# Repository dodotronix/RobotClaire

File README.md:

# ROBOT CLAIRE
This project is the result of three years of development from my high school
years. The main goal was to build my own robot from scratch, without using
common construction parts that are readily available in many hobbyist shops
today.

At the time when I was creating my robot, open-source CAD programs weren’t at a
sufficient level to design something that could be sent to a factory for
fabrication. For this reason, the mechanical design was created using Inventor
2013, while the electronic design was done using KiCad. The project has already
gone through three upgrades, but the first one wasn’t documented. However, I
did take some photos to capture the atmosphere of the very first steps in
development ([claire-rev0](https://drive.google.com/open?id=1PmOoYiifd_Xv0sS2DL9yxbEeKM7cLnv_)).

## NAVIGATION IN PROJECT
In the following folders, you will find README.md files with more detailed
descriptions of the content. Some folders also include additional information,
such as installation and execution instructions, particularly in directories
containing software. Please note that this repository is still under
development, and not all folders have been fully uploaded yet.

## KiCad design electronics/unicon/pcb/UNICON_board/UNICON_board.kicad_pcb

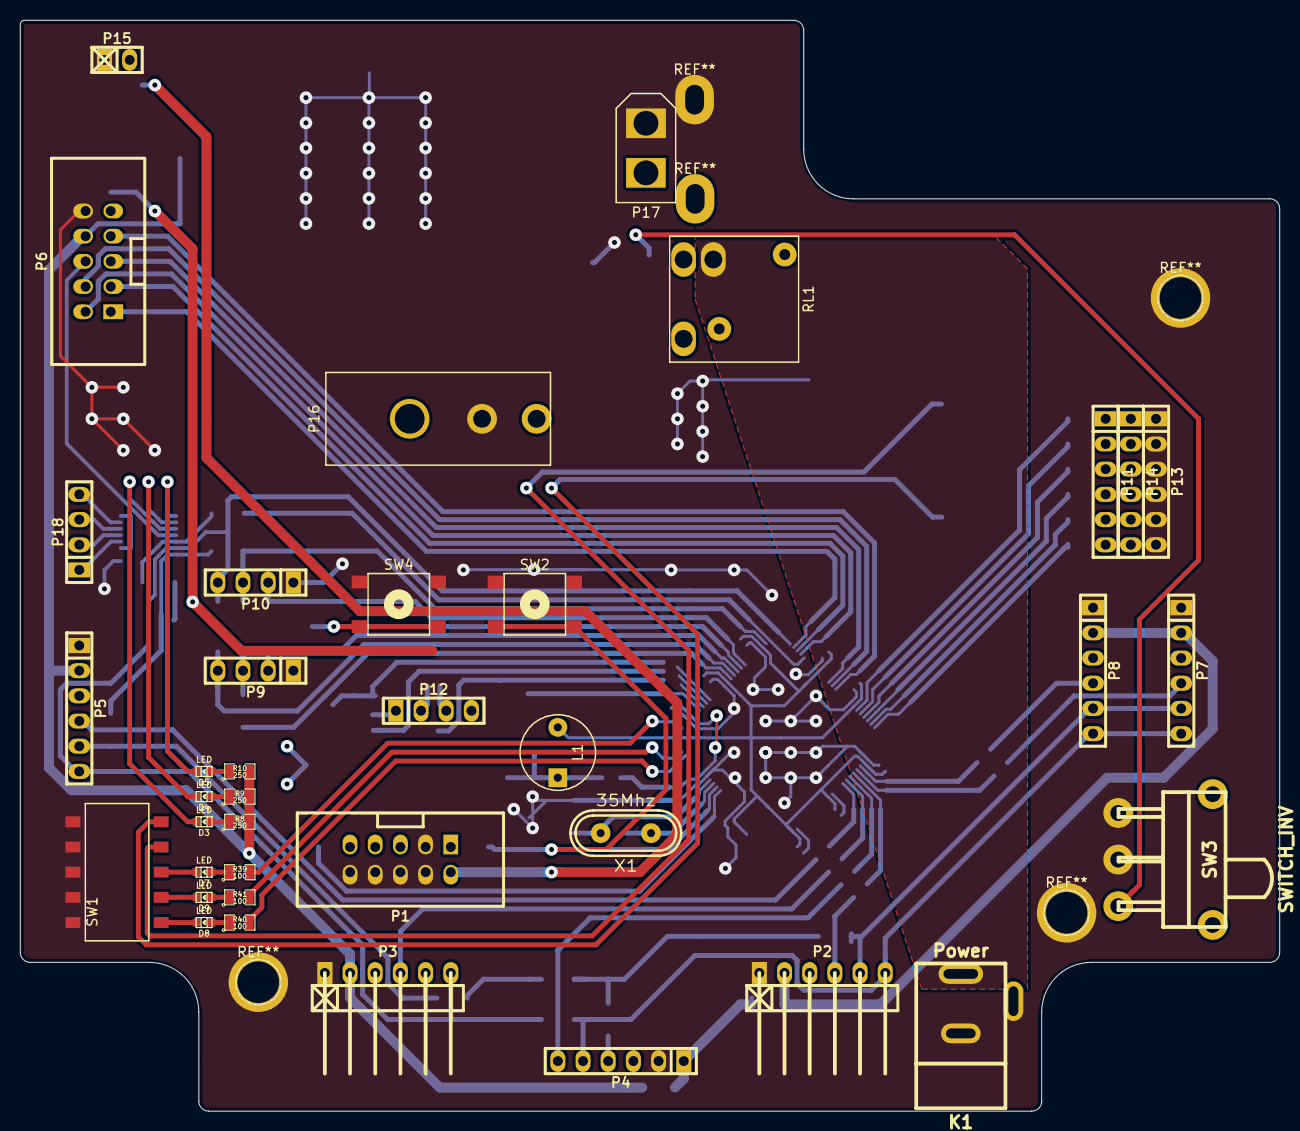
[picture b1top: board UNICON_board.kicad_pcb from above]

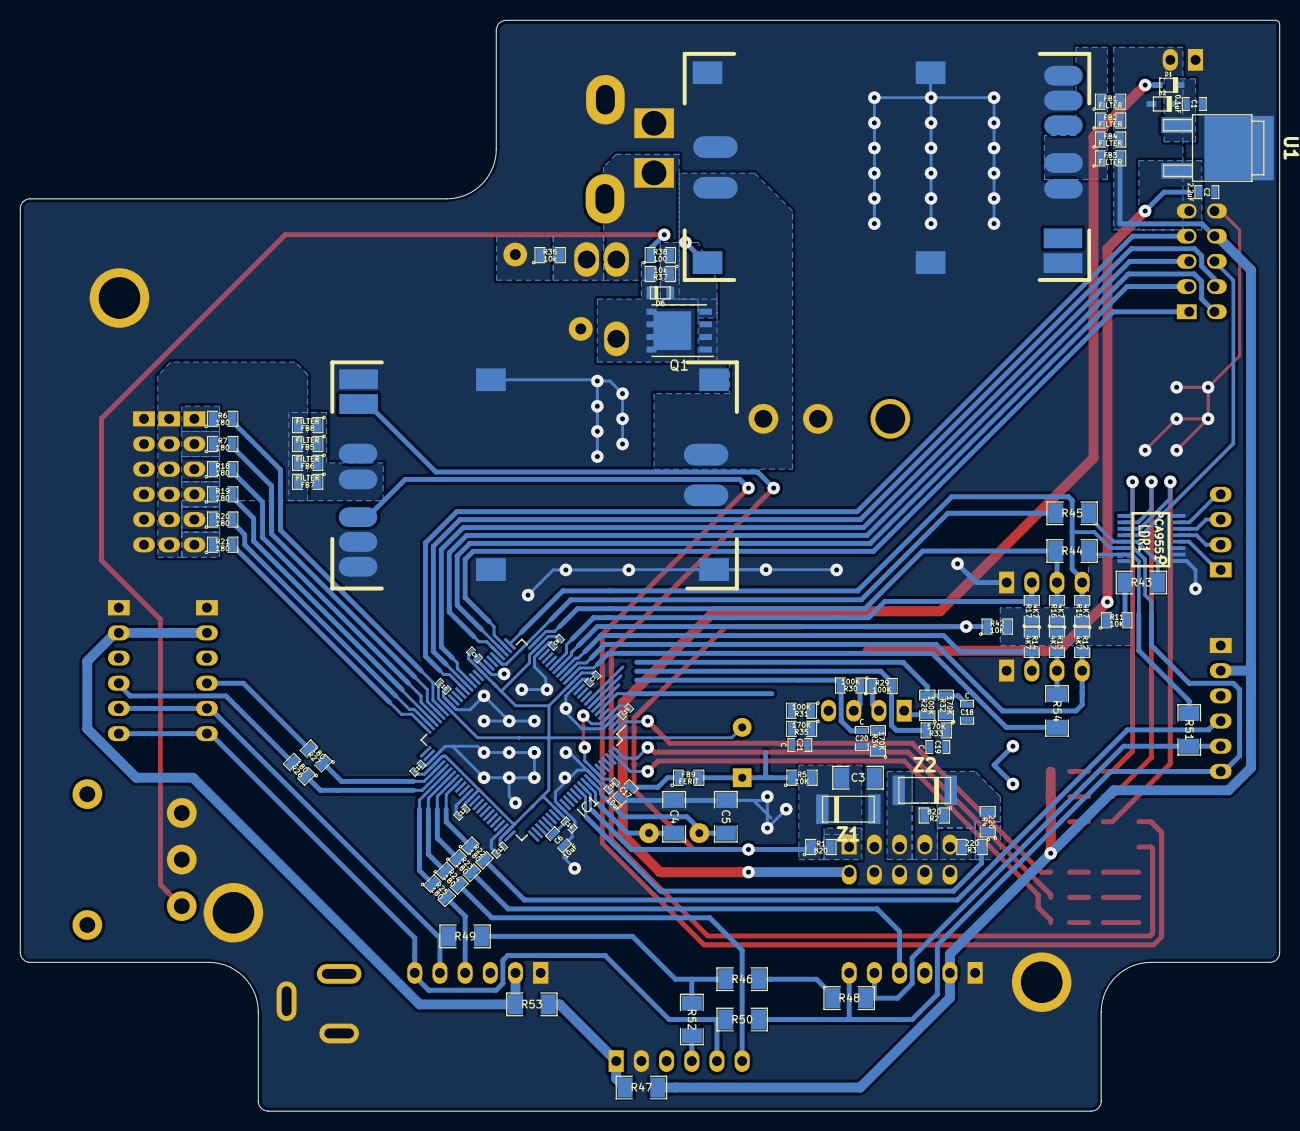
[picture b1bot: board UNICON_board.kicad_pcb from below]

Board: 2 copper layers, 127.0 x 110.0 mm, 127 parts (89 on the bottom side), 106 nets.

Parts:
C1: 0.1uF; SM0603_Capa
C2: 2.2uF; SM0603_Capa
C3, C4, C5: 22pF; SM1206
C6, C17: 10uF; SM0603_Capa
C7, C8, C9, C10, C11, C12, C13, C14, C15, C16: 100nF; SM0402
C18, C19, C20, C21: C; SM0603_Capa
D1, D2: DIODESCH; sod323
D3, D4, D5, D7, D8, D9: LED; Led_0603
D6: ZENER; micromelf
FB1, FB2, FB3, FB4, FB5, FB6, FB7, FB8: FILTER; SM0805
FB9: FERIT; SM0805
IC1: ATXMEGA64A1-A; TQFP-100_14x14mm_Pitch0.5mm
K1: Power; dc_socket
L1: 10uH; INDUCTOR_V
LDR1: PCA9551; TSSOP16
P1: CONN_5X2; vasch_strip_5x2
P2: Sens3; pin_strip_6-90
P3: Sens2; pin_strip_6-90
P4: compss; pin_socket_6
P5: Sens4; pin_strip_6
P6: Supp_board; vasch_strip_5x2
P7: Sens0; pin_strip_6
P8: Sens1; pin_strip_6
P9: I2C_1; pin_strip_4
P10: I2C_0; pin_strip_4
P11, P13, P14: CONN_6; pin_strip_6
P12: CONN_4; pin_strip_4
P15: RPI_supp; pin_strip_2
P16: Add_BRD; MOLEX_mega_fit_2
P17: BATT; XT30
P18: GPIOs; pin_strip_4
Q1: BS133; SO-8_PowerPAK_Vishay
R1, R2: 820; SM0805
R3, R4: 220; SM0805
R5, R11, R42: 10K; SM0805
R6, R7, R18, R19, R20, R21, R22, R23, R24, R25, R26, R27: 180; SM0805
R8, R9, R10: 250; SM0805
R12, R13, R14, R15, R16, R17: 4K7; SM0805
R28, R29, R30, R31: 100K; SM0805
R32, R33, R34, R35: 170K; SM0805
R36, R37: 10k; SM0805
R38, R39, R40, R41: 100; SM0805
R43, R44, R46, R47, R48, R49, R50, R51, R52, R53, R54: 0; SM1206
R45: 180; SM1206
RL1: relay; relay_TRS_L_12
S1, S2: UBEC(5A); UBEC_5A
SW1: DIPS_05; dip_switch_5
SW2: REBOOT; Button_smd
SW3: SWITCH_INV; switch_mfp116dg-ra
SW4: MODE; Button_smd
U1: LF33CDT; d-pak
X1: 35Mhz; crystal_hc-49s
Z1, Z2: 3V6; melf

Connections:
5Vin: D1.1, P1.2
5Vout: D2.1, FB1.2, FB2.2, FB3.2, FB4.2, P3.2, P5.2, P6.8, P15.2, R8.2, R9.2, R10.2, R47.1
+3v3: C2.1, FB9.2, L1.1, LDR1.16, P6.9, R5.1, R11.1, R12.1, R13.1, R14.1, R15.1, R16.1, R17.1, R42.2, U1.3
+6Vout: FB5.2, FB6.2, FB7.2, FB8.2, P14.1, P14.2, P14.3, P14.4, P14.5, P14.6
+12V: P16.2, Q1.1, S1.1, S2.1
ADC_0: C21.1, IC1.6, R31.2, R35.2
ADC_1: C20.1, IC1.7, R30.2, R34.2
ADC_2: C19.1, IC1.8, R29.2, R33.2
ADC_3: C18.1, IC1.9, R28.2, R32.2
CLK_PDI: C3.1, IC1.90, R1.1, R5.2, SW2.1, Z1.2
DT_PDI: IC1.89, R3.1, R4.1
GND: C1.2, C2.2, C3.2, C4.2, C5.2, C6.1, C7.1, C8.1, C9.1, C10.1, C11.1, C12.1, C13.1, C14.1, C15.1, C16.1, C17.1, C18.2, C19.2, C20.2, C21.2, IC1.3, IC1.13, IC1.23, IC1.33, IC1.43, IC1.53, IC1.63, IC1.73, IC1.84, IC1.93, K1.1, K1.2, LDR1.1, LDR1.2, LDR1.3, LDR1.8, P1.3, P1.4, P1.6, P1.8, P1.10, P2.1, P3.1, P4.2, P5.1, P6.10, P7.1, P8.1, P9.1, P10.1, P13.1, P13.2, P13.3, P13.4, P13.5, P13.6, P15.1, P16.1, P17.1, R32.1, R33.1, R34.1, R35.1, RL1.5, S1.5, S2.5, SW1.1, SW1.2, SW1.3, SW1.4, SW1.5, SW2.2, SW3.2, SW3.3, SW4.2, U1.2, Z1.1
I2C_0+: LDR1.15, R44.2, R51.1
I2C_0-: IC1.26, LDR1.14, P3.6, P5.6, P10.4, R15.2, R50.1
I2C_1+: IC1.15, R54.1
I2C_1-: IC1.16, P9.4, R12.2
INT_0: IC1.19, P10.2, R17.2
INT_1: IC1.17, P9.2, R14.2
INT_A_0: IC1.28, P6.3
INT_A_1: IC1.39, P6.7
INT_B_0: IC1.27, P6.1
INT_B_1: IC1.37, P6.5
Light: LDR1.12, P6.6
MTR_0: IC1.29, P6.2
MTR_1: IC1.38, P6.4
unnamed: C1.1, D1.2, D2.2, U1.1
unnamed: C4.1, IC1.91, X1.1
unnamed: C5.1, IC1.92, X1.2
unnamed: C6.2, C7.2, C8.2, C9.2, C10.2, C11.2, C12.2, C13.2, C14.2, IC1.14, IC1.24, IC1.34, IC1.44, IC1.54, IC1.64, IC1.74, IC1.83, L1.2
unnamed: C15.2, C16.2, C17.2, FB9.1, IC1.4, IC1.94
unnamed: D3.1, R8.1
unnamed: D3.2, LDR1.11
unnamed: D4.1, R9.1
unnamed: D4.2, LDR1.10
unnamed: D5.1, R10.1
unnamed: D5.2, LDR1.9
unnamed: D6.1, Q1.2, R37.1, R38.2
unnamed: D6.2, Q1.3, R37.2, RL1.3
unnamed: D7.1, R39.1
unnamed: D8.1, R40.1
unnamed: D9.1, R41.1
unnamed: FB1.1, FB2.1, FB3.1, FB4.1, S1.2
unnamed: FB5.1, FB6.1, FB7.1, FB8.1, S2.2
unnamed: IC1.1, R39.2
unnamed: IC1.18, R42.1, SW4.1
unnamed: IC1.25, P10.3, R16.2, R44.1
unnamed: IC1.30, R45.2
unnamed: IC1.45, R6.2
unnamed: IC1.46, R7.2
unnamed: IC1.47, R18.2
unnamed: IC1.48, R19.2
unnamed: IC1.49, R20.2
unnamed: IC1.50, R21.2
unnamed: IC1.55, R27.1
unnamed: IC1.56, R26.1
unnamed: IC1.57, R25.1
unnamed: IC1.58, R24.1
unnamed: IC1.59, R23.1
unnamed: IC1.60, R22.1
unnamed: IC1.99, R40.2
unnamed: IC1.100, R41.2
unnamed: K1.3, R36.2, RL1.2
unnamed: LDR1.4, P18.1
unnamed: LDR1.5, P18.2
unnamed: LDR1.6, P18.3
unnamed: LDR1.7, P18.4
unnamed: P1.1, R1.2
unnamed: P1.5, Z2.1
unnamed: P1.7, R2.2
unnamed: P1.9, R3.2
unnamed: P2.2, P7.2, P8.2, R53.2
unnamed: P2.5, P7.5, P8.5, R49.2
unnamed: P2.6, P4.5, P7.6, P8.6, R50.2
unnamed: P3.5, P5.5, R48.1, R51.2
unnamed: P4.1, R47.2, R53.1
unnamed: P4.4, R52.1
unnamed: P9.3, R13.2, R54.2
unnamed: P11.1, R6.1
unnamed: P11.2, R7.1
unnamed: P11.3, R18.1
unnamed: P11.4, R19.1
unnamed: P11.5, R20.1
unnamed: P11.6, R21.1
unnamed: P12.1, R28.1
unnamed: P12.2, R29.1
unnamed: P12.3, R30.1
unnamed: P12.4, R31.1
unnamed: P17.2, RL1.1
unnamed: R2.1, R4.2, Z2.2
unnamed: R11.2, R43.2
unnamed: R36.1, RL1.4
unnamed: R46.1, R48.2
unnamed: R46.2, R49.1, R52.2
ON/OFF: R38.1, SW3.1
RST: LDR1.13, R43.1, R45.1
SW0: S2.3, SW1.10
SW1: S2.4, SW1.9
SW2: D9.2, SW1.7
SW3: D8.2, SW1.6
SW4: D7.2, SW1.8
sens0int: P7.4, R26.2
sens1int: P8.4, R27.2
sens2int: P3.4, R23.2
sens3int: P2.4, R25.2
sens4int: P5.4, R22.2
speed_up: P4.6, R24.2

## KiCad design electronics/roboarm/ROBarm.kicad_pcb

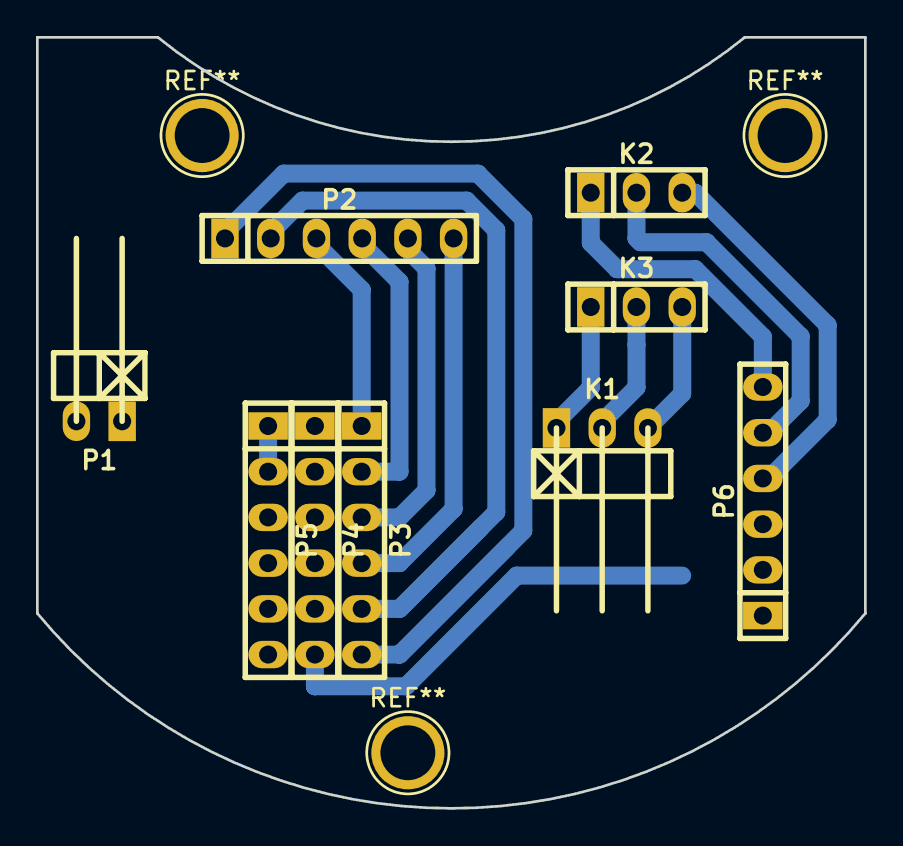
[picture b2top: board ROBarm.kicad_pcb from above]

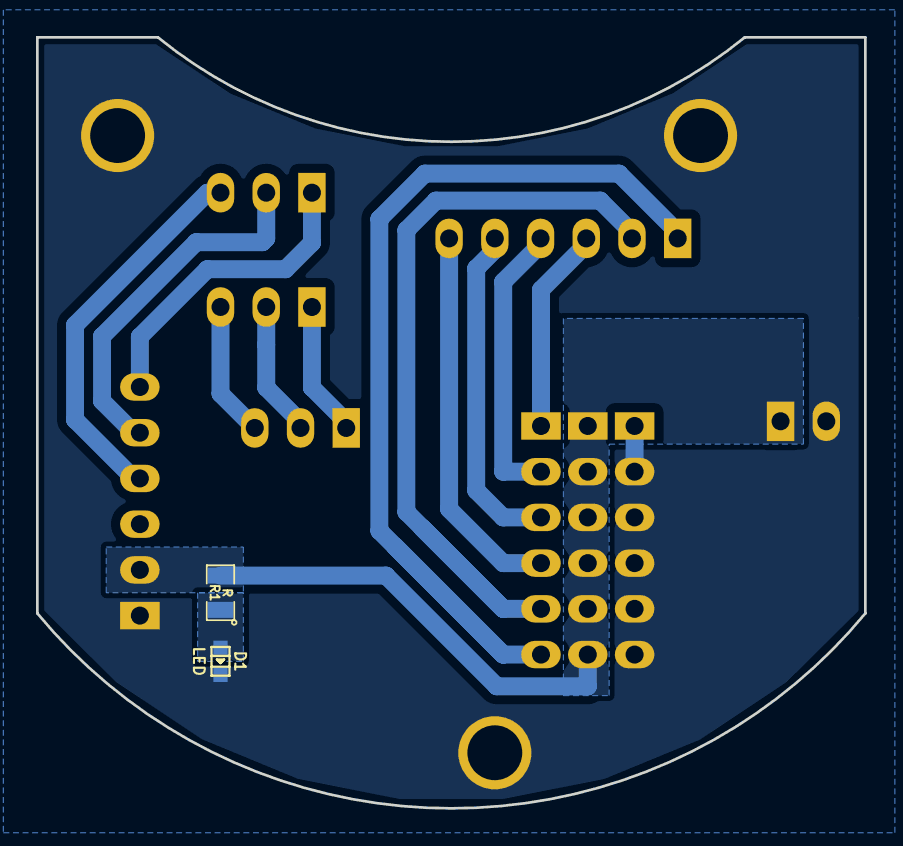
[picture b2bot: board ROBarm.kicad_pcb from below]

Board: 2 copper layers, 46.0 x 42.8 mm, 11 parts (2 on the bottom side), 15 nets.

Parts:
D1: LED; Led_0603
K1: CONN_3; pin_strip_3-90
K2, K3: CONN_3; pin_strip_3
P1: CONN_2; pin_strip_2-90
P2, P3, P4, P5, P6: CONN_6; pin_strip_6
R1: R; SM0805

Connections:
+6V: P1.1, P4.1, P4.2, P4.3, P4.4, P4.5, P4.6, P6.2, R1.2
GND: D1.2, P1.2, P5.1, P5.2, P5.3, P5.4, P5.5, P5.6, P6.1
IO_0: K2.3, P6.4
unnamed: D1.1, R1.1
PTCM+: K1.2, K3.2
PTCM-: K1.1, K3.1
PTCMs: K1.3, K3.3
SCL: K2.1, P6.6
SDA: K2.2, P6.5
SRV_0: P2.3, P3.1
SRV_1: P2.4, P3.2
SRV_2: P2.5, P3.3
SRV_3: P2.6, P3.4
SRV_4: P2.2, P3.5
SRV_5: P2.1, P3.6

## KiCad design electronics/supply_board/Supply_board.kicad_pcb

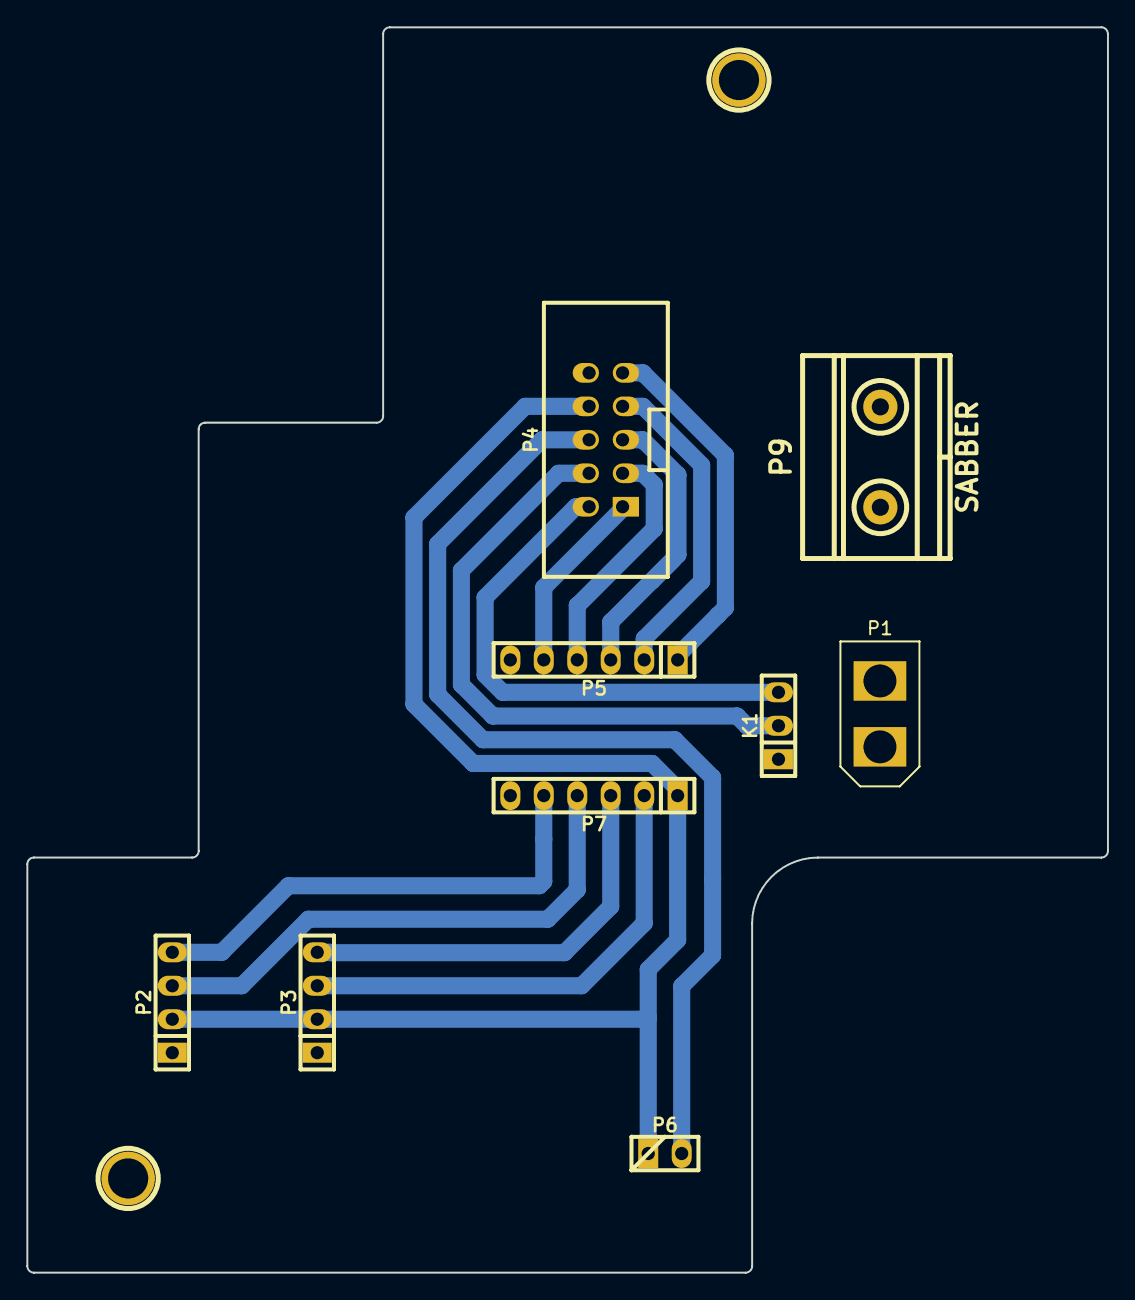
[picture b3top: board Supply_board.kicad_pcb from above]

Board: 2 copper layers, 82.0 x 94.5 mm, 11 parts (0 on the bottom side), 15 nets.

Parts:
1PIN, 2PIN: P***; 1pin
K1: SIG_MTR; pin_strip_3
P1: BATT; XT30
P2: ENK0; pin_strip_4
P3: ENK1; pin_strip_4
P4: SIGNALS; vasch_strip_5x2
P5, P7: LV_SHIFT; pin_socket_6
P6: LED_SIG; pin_strip_2
P9: SABBER; gmkds_3-2-7,62

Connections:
+3V3: P4.9, P5.1
+5V: P2.2, P3.2, P4.8, P6.1, P7.1
+12V: P1.2, P9.1
ENC_A_0: P2.3, P7.4
ENC_A_1: P3.3, P7.2
ENC_B_0: P2.4, P7.5
ENC_B_1: P3.4, P7.3
GND: 1PIN.2, 2PIN.1, K1.1, P1.1, P2.1, P3.1, P4.10, P5.6, P7.6, P9.2
INT_A_0: P4.3, P5.4
INT_A_1: P4.7, P5.2
INT_B_0: P4.1, P5.5
INT_B_1: P4.5, P5.3
LED: P4.6, P6.2
MTR_0: K1.3, P4.2
MTR_1: K1.2, P4.4

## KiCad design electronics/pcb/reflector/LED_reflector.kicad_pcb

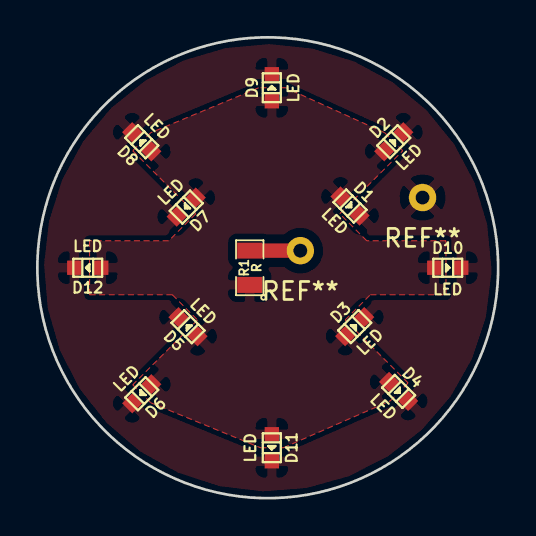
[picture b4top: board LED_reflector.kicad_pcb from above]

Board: 2 copper layers, 25.6 x 25.6 mm, 13 parts (0 on the bottom side), 2 nets.

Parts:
D1, D2, D3, D4, D5, D6, D7, D8, D9, D10, D11, D12: LED; Led_0603
R1: R; SM0805

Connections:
GND: D1.2, D2.2, D3.2, D4.2, D5.2, D6.2, D7.2, D8.2, D9.2, D10.2, D11.2, D12.2
unnamed: D1.1, D2.1, D3.1, D4.1, D5.1, D6.1, D7.1, D8.1, D9.1, D10.1, D11.1, D12.1, R1.1

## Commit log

2020-01-30 new README.md
2020-01-30 created introduction - readme
2020-01-30 text correction - share link
2020-01-30 text correction - readme
2020-01-30 added video link - readme
2020-02-05 added CAD model from inventor 2013
2020-02-05 added reflector pcb design
2020-02-19 markdown syntax test - introduction photo
2020-02-19 shared picture fixed markdown syntax
2020-02-19 shared picture from google disk - fetching test
2020-03-22 Robot_system.drawio
2020-03-22 Robot_system.svg
2020-03-22 drawings moved to doc folder
2020-03-22 new submodules sensors
2020-03-29 changed size of themain picture
2020-03-29 bigger size of main picture
2020-03-29 main picture change of size
2020-09-30 Raw files from original project Robot Claire
2020-09-30 updated module sensors
2025-04-02 updated readme picture
2025-04-02 fixed readme
2025-04-02 Readme update
